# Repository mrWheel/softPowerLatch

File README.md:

# Soft Power Latch
## Disclaimer

This hardware is developed incrementally. That means I have no clear idea how it works (though it mostly does).

If you have questions about this software, it will probably take you just as long to figure things out as it would take me. So I’d prefer that you investigate it yourself.

Having said that ***Don’t Even Think About Using It***

Seriously. Don’t.

Building this design may injure or kill you during construction, burn your house down while in use, and then—just to be thorough—explode afterward.

This is not a joke. This project involves lethal voltages. If you are not a qualified electronics engineer, close this repository, step away from the soldering iron, and make yourself a cup of tea.

If you decide to ignore all of the above and build it anyway, you do so ***entirely at your own risk***. You are fully responsible for taking proper safety precautions. I take zero responsibility for anything that happens—electrically, mechanically, chemically, spiritually, or otherwise.

Also, full disclosure: *I am not a qualified electrical engineer*. I provide no guarantees, no warranties, and absolutely no assurance that this design is correct, safe, or suitable for any purpose whatsoever.

## What it is
A simple and efficient soft power latch circuit that allows a device to be switched on and off using a single push button, with ultra-low standby current.

<div align="center">

</div>

This project is based on the design described by Willem Aandewiel.

## Features
	•	Single push-button ON/OFF control
	•	Ultra-low standby current (µA range)
	•	Suitable for battery-powered devices
	•	Works with Li-Ion (e.g. 18650) + boost converter
	•	Minimal component count
	•	Reliable latch behavior

## Overview

This circuit provides a latching power switch using discrete components.
A short button press toggles the power state:

	•	First press → Power ON
	•	Second press → Power OFF

Unlike a mechanical switch, this solution allows:

	•	electronic control
	•	low standby consumption
	•	integration with microcontroller systems

## How It Works

### Initial State (OFF)
	•	The battery is connected but the circuit is inactive
	•	The MOSFET is OFF
	•	No current flows to the load
	•	Capacitor is uncharged

### First Button Press (Power ON)
	•	The capacitor pulls the MOSFET gate low
	•	The MOSFET turns ON
	•	Output voltage rises to V+

#### Then the latch is formed:
	•	The transistor turns ON
	•	It keeps the MOSFET gate low
	•	The circuit stays ON after releasing the button

### Second Button Press (Power OFF)
	•	The capacitor is now charged
	•	Pressing the button breaks the latch
	•	The transistor turns OFF
	•	The MOSFET gate is pulled high
	•	Power is disconnected

This creates a reliable toggle behavior with a single button.  ￼

## Circuit Notes
	•	A small load resistor improves stability
	•	A Schottky diode is recommended when:
  	 •	driving motors
	 •	using boost converters (prevents backfeed issues)  ￼

## Hardware

### The repository contains:
	•	Schematic (KiCad)
	•	PCB design
	•	Gerber files for manufacturing

All symbols, footprint and 3D files are stored in and referenced by ```localLibs```

<div align="center">

</div>

## Power Configuration

### Typical setup:
	•	Battery: Li-Ion (18650)
	•	Charging module: standard TP4056
	•	Step-up converter: 5V output

### Use Cases
	•	Battery-powered microcontroller projects
	•	Portable IoT devices
	•	DIY gadgets with a single-button interface
	•	Retro or embedded systems

## Advantages
	•	No mechanical power switch required
	•	Very low standby consumption
	•	Simple and inexpensive
	•	Easy to integrate into existing designs

## Limitations
	•	Not intended for high-current switching without proper MOSFET selection
	•	Requires careful component selection for stability

## Credits

Design and concept by
Willem Aandewiel

Original article:
https://willem.aandewiel.nl/index.php/2026/04/07/soft-power-latch-2/

## License

MIT License

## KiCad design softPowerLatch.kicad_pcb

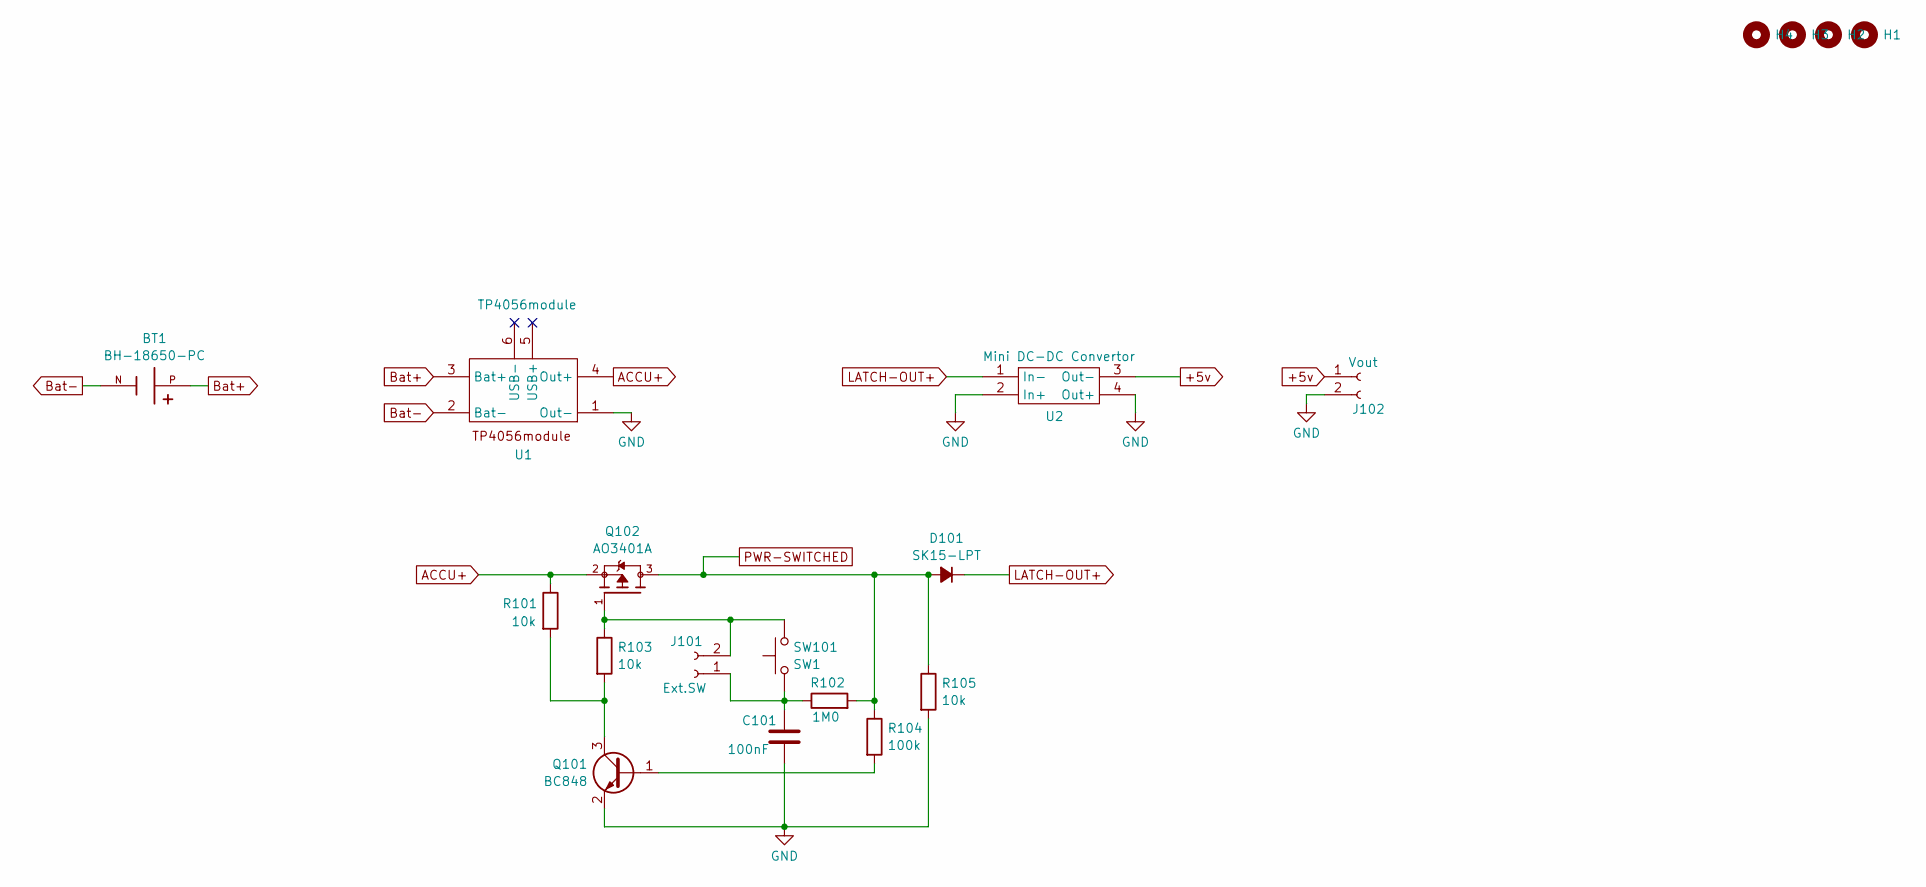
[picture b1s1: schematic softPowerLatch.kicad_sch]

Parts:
BT1: BH-18650-PC; BAT_BH-18650-PC; PARTREV 05/17/19
C101: 100nF; C_1206_3216Metric_Pad1.33x1.80mm_HandSolder
D101: SK15-LPT; D_SMA-SMB_Universal_Handsoldering
H1, H2, H3, H4: MountingHole; MountingHole_3.2mm_M3
J101: Ext.SW; JST_XH_B2B-XH-A_1x02_P2.50mm_Vertical
J102: Vout; JST_XH_B2B-XH-A_1x02_P2.50mm_Vertical
Q101: BC848; SOT-23
Q102: AO3401A; AO3401
R101, R103, R105: 10k; R_1206_3216Metric_Pad1.30x1.75mm_HandSolder
R102: 1M0; R_1206_3216Metric_Pad1.30x1.75mm_HandSolder
R104: 100k; R_1206_3216Metric_Pad1.30x1.75mm_HandSolder
SW101: SW1; SW_PUSH_6mm_H5mm
U1: TP4056module; TP4056_USB-Charger_Board
U2: Mini DC-DC Convertor; Mini_DC-DC_Boost_Convertor

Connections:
+5v: J102.1, U2.3 (Out-)
ACCU+: Q102.2, R101.1, U1.4 (Out+)
Bat+: BT1.P, U1.3 (Bat+)
Bat-: BT1.N, U1.2 (Bat-)
GND: C101.2, J102.2, Q101.2 (E), R105.2, U1.1 (Out-), U2.2 (In+), U2.4 (Out+)
LATCH-OUT+: D101.1 (K), U2.1 (In-)
unnamed: C101.1, J101.1, R102.1, SW101.1
unnamed: J101.2, Q102.1, R103.1, SW101.2
unnamed: Q101.1 (B), R104.2
unnamed: Q101.3 (C), R101.2, R103.2
PWR-SWITCHED: D101.2 (A), Q102.3, R102.2, R104.1, R105.1

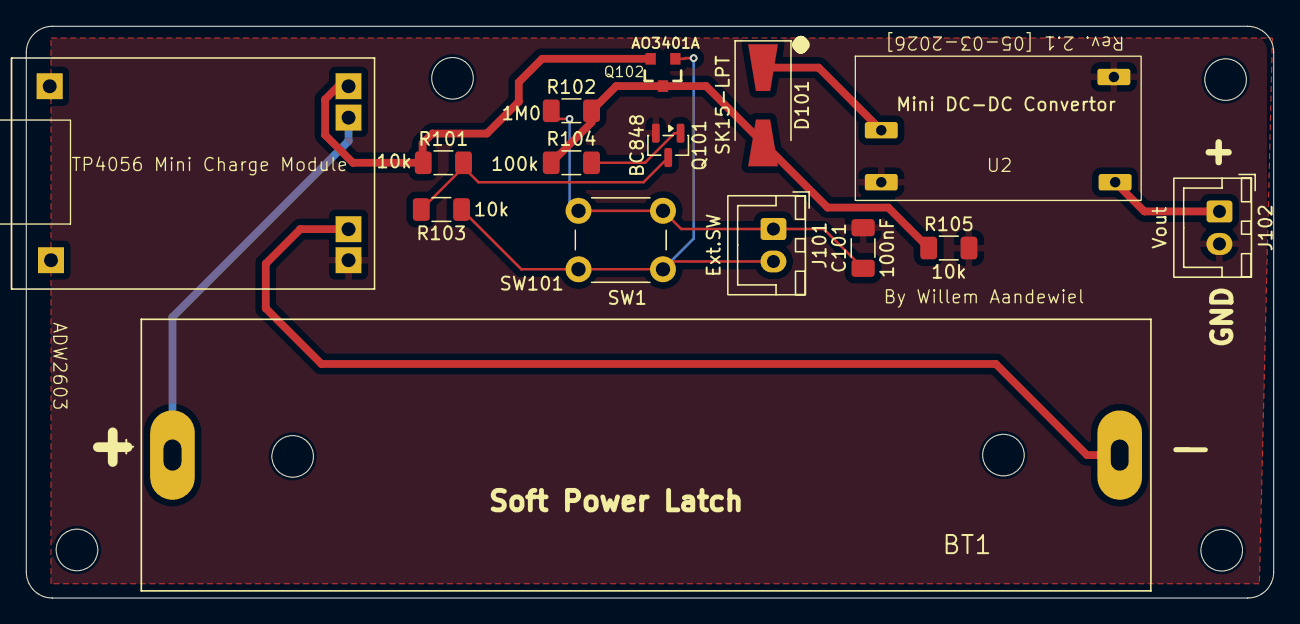
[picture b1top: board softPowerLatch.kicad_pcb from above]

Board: 2 copper layers, 96.0 x 44.0 mm, 19 parts (0 on the bottom side), 11 nets.

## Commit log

2026-04-12 First Commit KiCad 9.0.7
2026-04-12 Add sync_backup to .gitignore
2026-04-13 Create README.md for Soft Power Latch project
    Add detailed documentation for the Soft Power Latch project.
2026-04-13 Add MIT License to the project
2026-04-17 Renamed "images" to "assets" Added disclamer to README.md
2026-04-17 Typo
